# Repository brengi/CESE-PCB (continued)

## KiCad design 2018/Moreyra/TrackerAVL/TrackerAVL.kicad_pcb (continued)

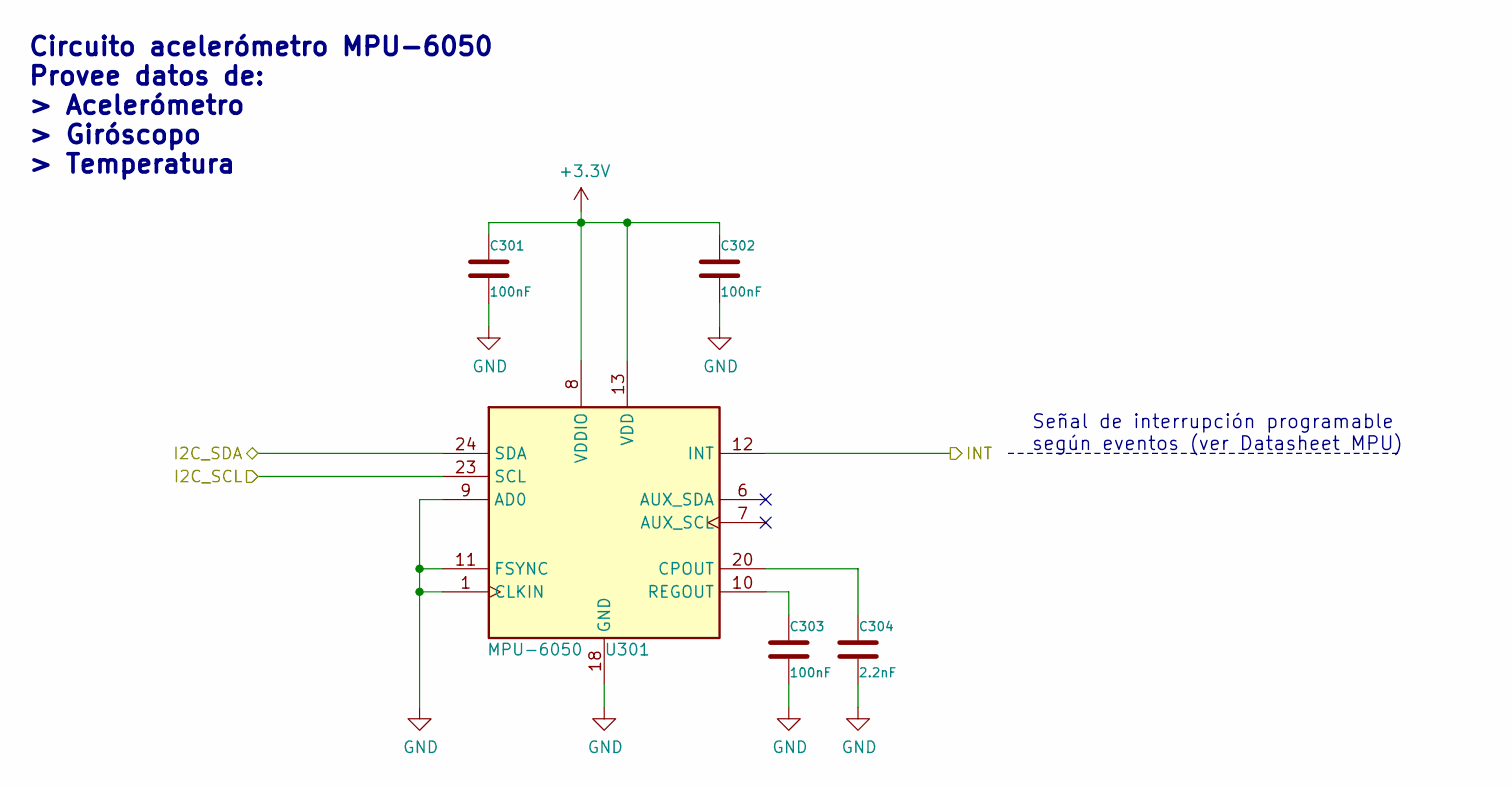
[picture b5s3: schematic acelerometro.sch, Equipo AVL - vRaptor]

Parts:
C301, C302, C303: 100nF; C_0805_2012Metric_Pad1.15x1.40mm_HandSolder
C304: 2.2nF; C_0805_2012Metric_Pad1.15x1.40mm_HandSolder
U301: MPU-6050; InvenSense_QFN-24_4x4mm_P0.5mm

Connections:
+3V3: C301.1, C302.1, U301.8 (VDDIO), U301.13 (VDD); also elsewhere on the board
/Acelerómetro/INT: U301.12 (INT); also elsewhere on the board
/I2C_SCL: U301.23 (SCL); also elsewhere on the board
/I2C_SDA: U301.24 (SDA); also elsewhere on the board
GND: C301.2, C302.2, C303.2, C304.2, U301.1 (CLKIN), U301.9 (AD0), U301.11 (FSYNC), U301.18 (GND); also elsewhere on the board
unnamed: C303.1, U301.10 (REGOUT)
unnamed: C304.1, U301.20 (CPOUT)

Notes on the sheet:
Circuito acelerómetro MPU-6050 Provee datos de: > Acelerómetro > Giróscopo > Temperatura
Señal de interrupción programable según eventos (ver Datasheet MPU)

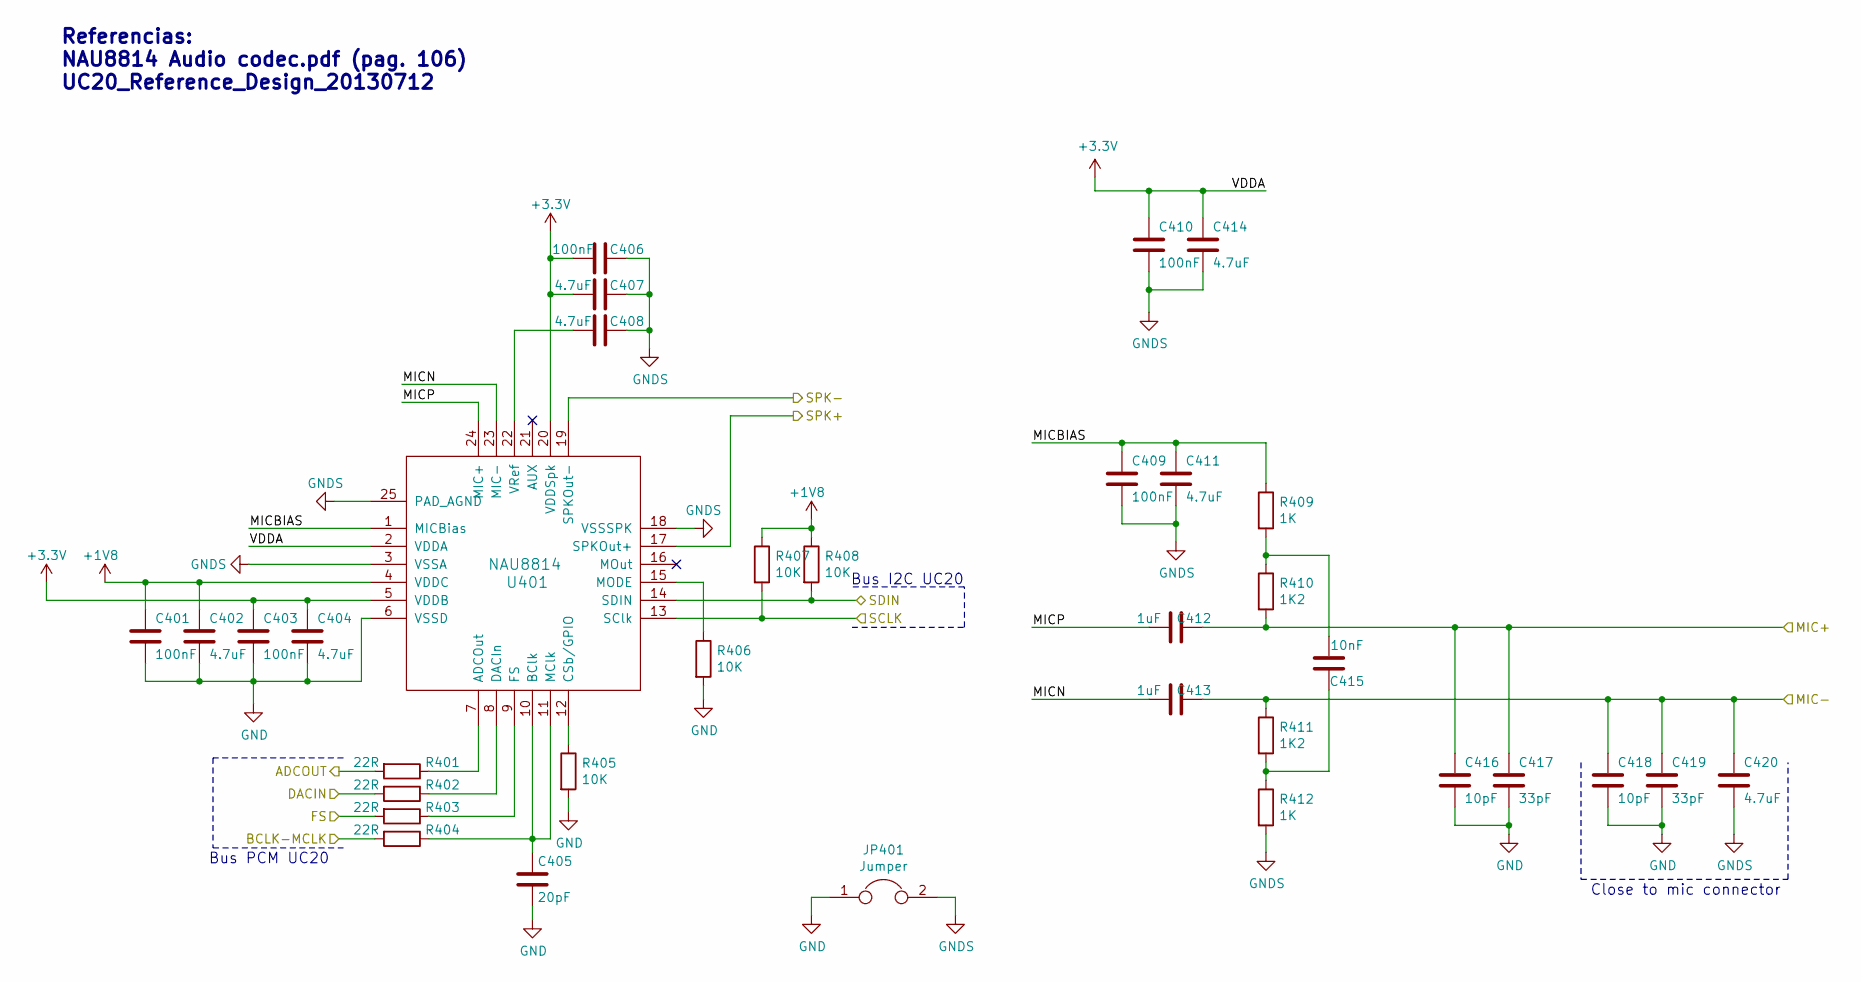
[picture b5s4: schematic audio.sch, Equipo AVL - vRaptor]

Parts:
C401, C403, C406, C409, C410: 100nF; C_0805_2012Metric_Pad1.15x1.40mm_HandSolder
C402, C404, C407, C408, C411, C414, C420: 4.7uF; C_0805_2012Metric_Pad1.15x1.40mm_HandSolder
C405: 20pF; C_0805_2012Metric_Pad1.15x1.40mm_HandSolder
C412, C413: 1uF; C_0805_2012Metric_Pad1.15x1.40mm_HandSolder
C415: 10nF; C_0805_2012Metric_Pad1.15x1.40mm_HandSolder
C416, C418: 10pF; C_0805_2012Metric_Pad1.15x1.40mm_HandSolder
C417, C419: 33pF; C_0805_2012Metric_Pad1.15x1.40mm_HandSolder
JP401: Jumper; SolderJumper-2_P1.3mm_Bridged_Pad1.0x1.5mm
R401, R402, R403, R404: 22R; R_0805_2012Metric_Pad1.15x1.40mm_HandSolder
R405, R406, R407, R408: 10K; R_0805_2012Metric_Pad1.15x1.40mm_HandSolder
R409, R412: 1K; R_0805_2012Metric_Pad1.15x1.40mm_HandSolder
R410, R411: 1K2; R_0805_2012Metric_Pad1.15x1.40mm_HandSolder
U401: NAU8814; NAU8814_QFN-24_4x4mm_Pitch0.5mm_EPAD

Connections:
+1V8: C401.1, C402.1, R407.1, R408.1, U401.4 (VDDC); also elsewhere on the board
+3V3: C403.1, C404.1, C406.1, C407.1, C410.1, C414.1, U401.2 (VDDA), U401.5 (VDDB), U401.20 (VDDSpk); also elsewhere on the board
/Audio/ADCOUT: R401.2; also elsewhere on the board
/Audio/BCLK-MCLK: R404.2; also elsewhere on the board
/Audio/DACIN: R402.2; also elsewhere on the board
/Audio/FS: R403.2; also elsewhere on the board
/Audio/MICBIAS: C409.1, C411.1, R409.1, U401.1 (MICBias)
/Audio/MICN: C413.1, U401.23 (MIC-)
/Audio/MICP: C412.1, U401.24 (MIC+)
/MIC+: C412.2, C416.1, C417.1, R410.2; also elsewhere on the board
/MIC-: C413.2, C418.1, C419.1, C420.1, R411.1; also elsewhere on the board
/SPK+: U401.17 (SPKOut+); also elsewhere on the board
/SPK-: U401.19 (SPKOut-); also elsewhere on the board
/UC20_PCIe/I2C_SCL: R407.2, U401.13 (SClk); also elsewhere on the board
/UC20_PCIe/I2C_SDA: R408.2, U401.14 (SDIN); also elsewhere on the board
GND: C401.2, C402.2, C403.2, C404.2, C405.2, C416.2, C417.2, C418.2, C419.2, JP401.1, R405.2, R406.2, U401.6 (VSSD); also elsewhere on the board
GNDS: C406.2, C407.2, C408.2, C409.2, C410.2, C411.2, C414.2, C420.2, JP401.2, R412.2, U401.3 (VSSA), U401.18 (VSSSPK), U401.25 (PAD_AGND)
unnamed: C405.1, R404.1, U401.10 (BClk), U401.11 (MClk)
unnamed: C408.1, U401.22 (VRef)
unnamed: C415.1, R409.2, R410.1
unnamed: C415.2, R411.2, R412.1
unnamed: R401.1, U401.7 (ADCOut)
unnamed: R402.1, U401.8 (DACIn)
unnamed: R403.1, U401.9 (FS)
unnamed: R405.1, U401.12 (CSb/GPIO)
unnamed: R406.1, U401.15 (MODE)

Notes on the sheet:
Referencias: NAU8814 Audio codec.pdf (pag. 106) UC20_Reference_Design_20130712
Close to mic connector
Bus I2C UC20
Bus PCM UC20

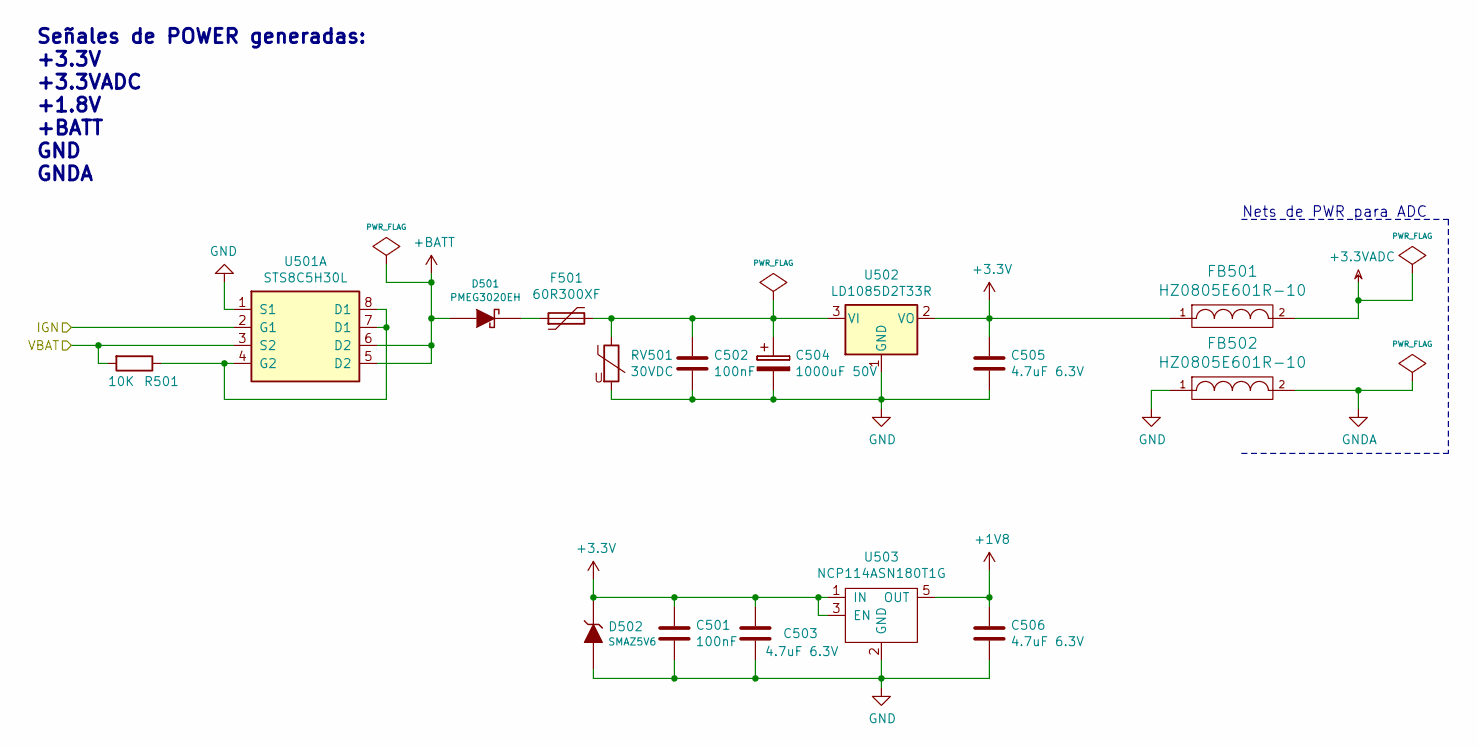
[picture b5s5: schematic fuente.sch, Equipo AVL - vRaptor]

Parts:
C501, C502: 100nF; C_0805_2012Metric_Pad1.15x1.40mm_HandSolder
C503, C505, C506: 4.7uF 6.3V; C_0805_2012Metric_Pad1.15x1.40mm_HandSolder
C504: 1000uF 50V; CP_Radial_D12.5mm_P5.00mm
D501: PMEG3020EH; D_SOD-123F
D502: SMAZ5V6; DO-214AC (SMA)
F501: 60R300XF
FB501, FB502: HZ0805E601R-10; L_0805_2012Metric_Pad1.15x1.40mm_HandSolder
R501: 10K; R_0805_2012Metric_Pad1.15x1.40mm_HandSolder
RV501: 30VDC; D_1206_3216Metric_Pad1.42x1.75mm_HandSolder
U501: STS8C5H30L; SOIC-8_3.9x4.9mm_P1.27mm
U502: LD1085D2T33R; TO-263-3_TabPin2
U503: NCP114ASN180T1G; TSOP-5_NCP114

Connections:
+1V8: C506.1, U503.5 (OUT); also elsewhere on the board
+3.3VADC: FB501.2; also elsewhere on the board
+3V3: C501.1, C503.1, C505.1, D502.2 (K), FB501.1, U502.2 (VO), U503.1 (IN), U503.3 (EN); also elsewhere on the board
+BATT: D501.1 (A), U501.5 (D2), U501.6 (D2)
/IGN: U501.2 (G1); also elsewhere on the board
/VBAT: R501.2, U501.3 (S2); also elsewhere on the board
GND: C501.2, C502.2, C503.2, C504.2, C505.2, C506.2, D502.1 (A), FB502.1, RV501.2, U501.1 (S1), U502.1 (GND), U503.2 (GND); also elsewhere on the board
GNDA: FB502.2; also elsewhere on the board
unnamed: C502.1, C504.1, F501.2, RV501.1, U502.3 (VI)
unnamed: D501.2 (K), F501.1
unnamed: R501.1, U501.4 (G2), U501.7 (D1), U501.8 (VSS)

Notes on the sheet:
Nets de PWR para ADC
Señales de POWER generadas: +3.3V +3.3VADC +1.8V +BATT GND GNDA

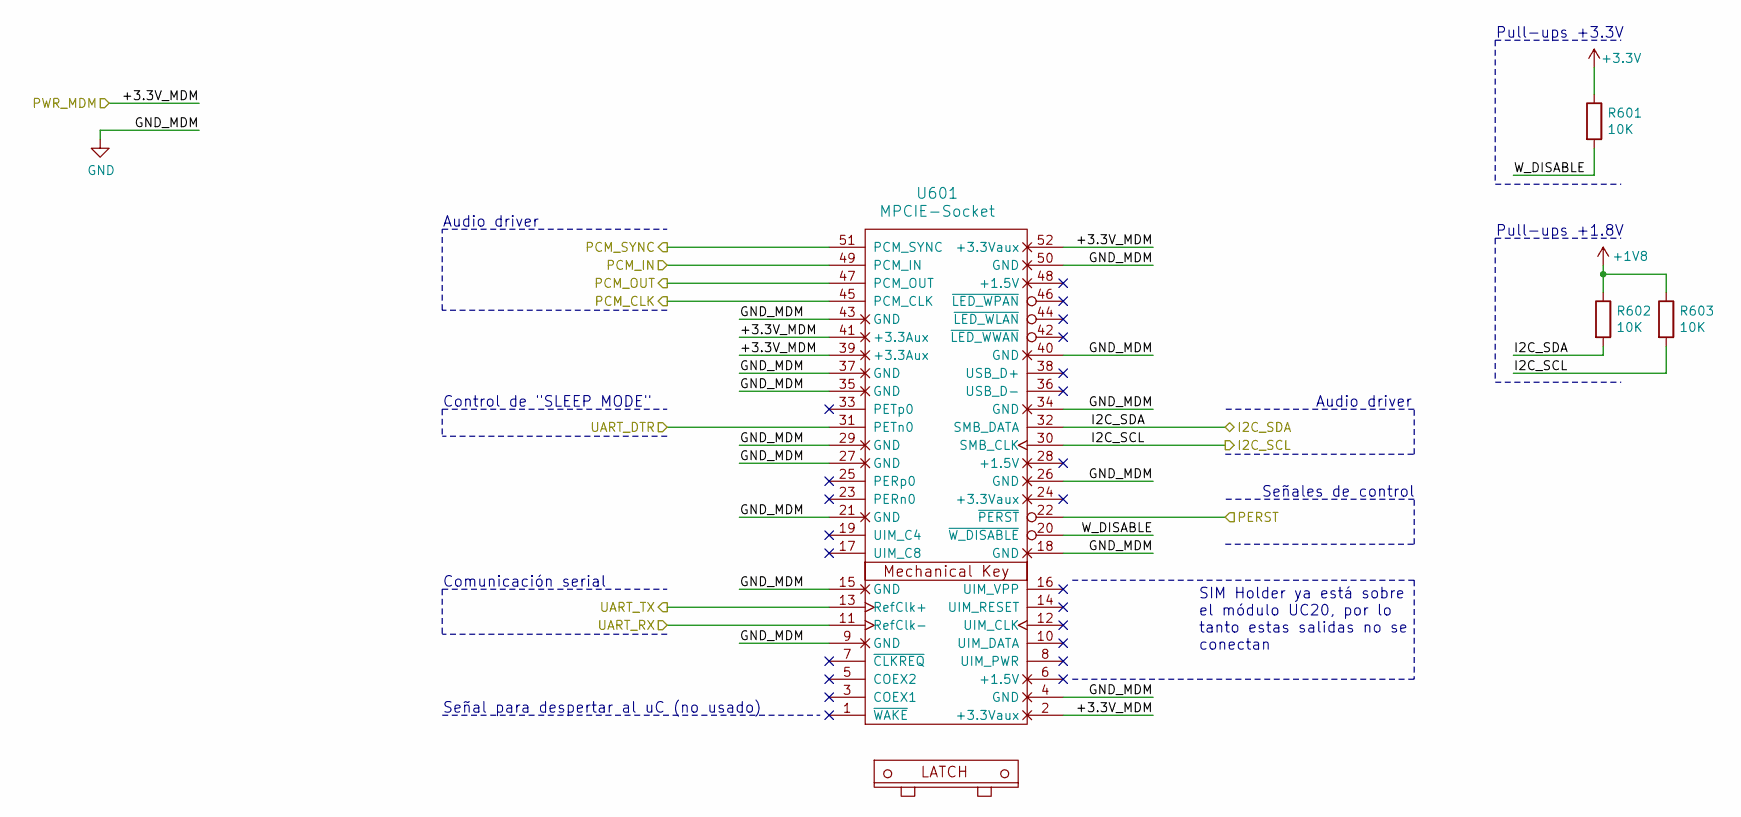
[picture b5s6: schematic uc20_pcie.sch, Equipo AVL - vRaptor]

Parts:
R601, R602, R603: 10K; R_0805_2012Metric_Pad1.15x1.40mm_HandSolder
U601: MPCIE-Socket; mpcie-socket-latch

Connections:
+1V8: R602.1, R603.1; also elsewhere on the board
+3V3: R601.1; also elsewhere on the board
/Audio/ADCOUT: U601.49 (PCM_IN); also elsewhere on the board
/Audio/BCLK-MCLK: U601.45 (PCM_CLK); also elsewhere on the board
/Audio/DACIN: U601.47 (PCM_OUT); also elsewhere on the board
/Audio/FS: U601.51 (PCM_SYNC); also elsewhere on the board
/CPU/PERST: U601.22 (~PERST); also elsewhere on the board
/CPU/PWR_MDM: U601.2 (+3.3Vaux), U601.39 (+3.3Aux), U601.41 (+3.3Aux), U601.52 (+3.3Vaux); also elsewhere on the board
/CPU/SLEEP_MDM: U601.31 (PETn0); also elsewhere on the board
/CPU/U3_RX: U601.13 (RefClk+); also elsewhere on the board
/CPU/U3_TX: U601.11 (RefClk-); also elsewhere on the board
/UC20_PCIe/I2C_SCL: R603.2, U601.30 (SMB_CLK); also elsewhere on the board
/UC20_PCIe/I2C_SDA: R602.2, U601.32 (SMB_DATA); also elsewhere on the board
/UC20_PCIe/W_DISABLE: R601.2, U601.20 (~W_DISABLE)
GND: U601.4 (GND), U601.9 (GND), U601.15 (GND), U601.18 (GND), U601.21 (GND), U601.26 (GND), U601.27 (GND), U601.29 (GND), U601.34 (GND), U601.35 (GND), U601.37 (GND), U601.40 (GND), U601.43 (GND), U601.50 (GND); also elsewhere on the board

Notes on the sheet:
Control de "SLEEP MODE"
Audio driver
Comunicación serial
Pull-ups +3.3V
Pull-ups +1.8V
Señales de control
SIM Holder ya está sobre el módulo UC20, por lo tanto estas salidas no se conectan
Señal para despertar al uC (no usado)

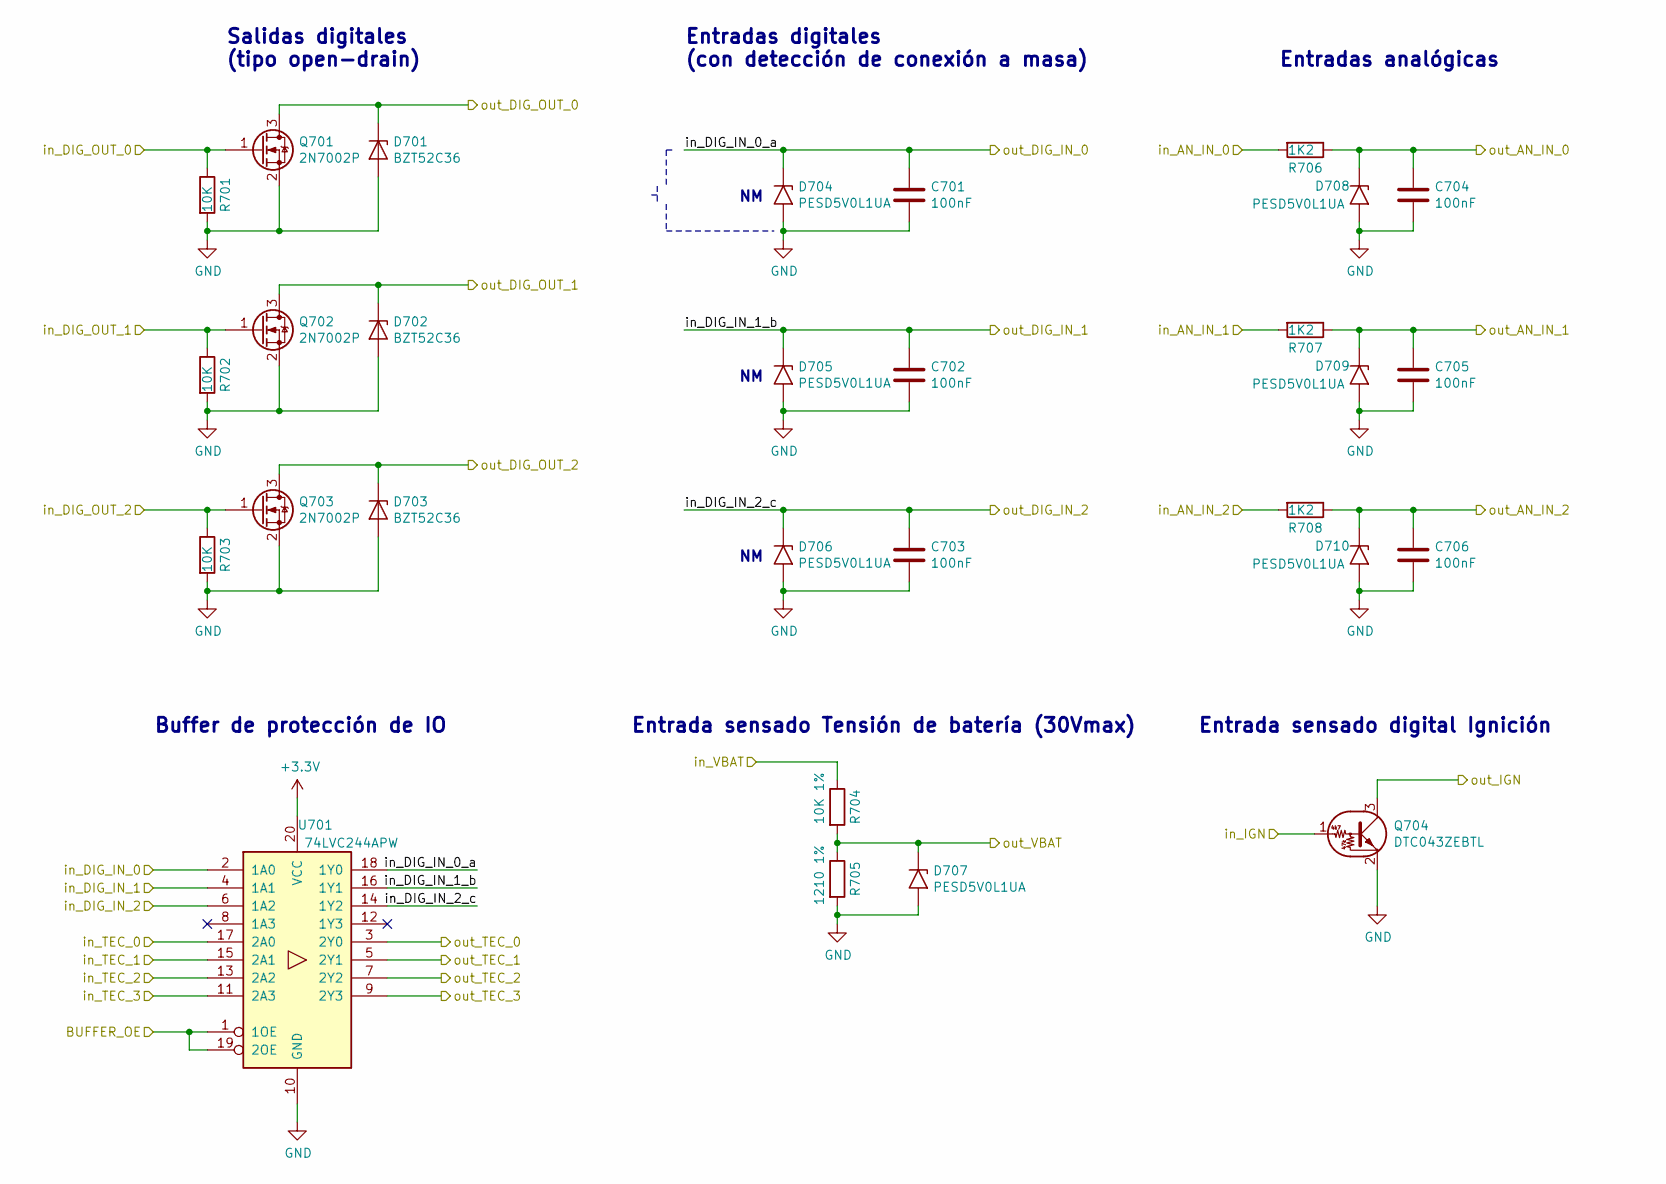
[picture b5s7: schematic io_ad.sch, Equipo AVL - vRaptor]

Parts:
C701, C702, C703, C704, C705, C706: 100nF; C_0805_2012Metric_Pad1.15x1.40mm_HandSolder
D701, D702, D703: BZT52C36; D_SOD-123
D704, D705, D706, D707, D708, D709, D710: PESD5V0L1UA; D_SOD-323_HandSoldering
Q701, Q702, Q703: 2N7002P; SOT-23_Handsoldering
Q704: DTC043ZEBTL; SOT-523_(SOT-416)
R701, R702, R703: 10K; R_0805_2012Metric_Pad1.15x1.40mm_HandSolder
R704: 10K 1%; R_0805_2012Metric_Pad1.15x1.40mm_HandSolder
R705: 1210 1%; R_0805_2012Metric_Pad1.15x1.40mm_HandSolder
R706, R707, R708: 1K2; R_0805_2012Metric_Pad1.15x1.40mm_HandSolder
U701: 74LVC244APW; TSSOP-20_4.4x6.5mm_P0.65mm

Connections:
+3V3: U701.20 (VCC); also elsewhere on the board
/AN_IN_0: R706.2; also elsewhere on the board
/AN_IN_1: R707.2; also elsewhere on the board
/AN_IN_2: R708.2; also elsewhere on the board
/CPU/AN_IN_0: C704.1, D708.1 (A1), R706.1; also elsewhere on the board
/CPU/AN_IN_1: C705.1, D709.1 (A1), R707.1; also elsewhere on the board
/CPU/AN_IN_2: C706.1, D710.1 (A1), R708.1; also elsewhere on the board
/CPU/BUFFER_OE: U701.1 (1OE), U701.19 (2OE); also elsewhere on the board
/CPU/DIG_IN_0: C701.1, D704.1 (A1), U701.18 (1Y0); also elsewhere on the board
/CPU/DIG_IN_1: C702.1, D705.1 (A1), U701.16 (1Y1); also elsewhere on the board
/CPU/DIG_IN_2: C703.1, D706.1 (A1), U701.14 (1Y2); also elsewhere on the board
/CPU/DIG_OUT_0: Q701.1 (G), R701.1; also elsewhere on the board
/CPU/DIG_OUT_1: Q702.1 (G), R702.1; also elsewhere on the board
/CPU/DIG_OUT_2: Q703.1 (G), R703.1; also elsewhere on the board
/CPU/IGN: Q704.3 (C); also elsewhere on the board
/CPU/TEC_0: U701.3 (2Y0); also elsewhere on the board
/CPU/TEC_1: U701.5 (2Y1); also elsewhere on the board
/CPU/TEC_2: U701.7 (2Y2); also elsewhere on the board
/CPU/TEC_3: U701.9 (2Y3); also elsewhere on the board
/CPU/VBAT: D707.1 (A1), R704.2, R705.1; also elsewhere on the board
/DIG_IN_0: U701.2 (1A0); also elsewhere on the board
/DIG_IN_1: U701.4 (1A1); also elsewhere on the board
/DIG_IN_2: U701.6 (1A2); also elsewhere on the board
/DIG_OUT_0: D701.1 (K), Q701.3 (D); also elsewhere on the board
/DIG_OUT_1: D702.1 (K), Q702.3 (D); also elsewhere on the board
/DIG_OUT_2: D703.1 (K), Q703.3 (D); also elsewhere on the board
/IGN: Q704.1 (B); also elsewhere on the board
/TEC_0: U701.17 (2A0); also elsewhere on the board
/TEC_1: U701.15 (2A1); also elsewhere on the board
/TEC_2: U701.13 (2A2); also elsewhere on the board
/TEC_3: U701.11 (2A3); also elsewhere on the board
/VBAT: R704.1; also elsewhere on the board
GND: C701.2, C702.2, C703.2, C704.2, C705.2, C706.2, D701.2 (A), D702.2 (A), D703.2 (A), D704.2 (A2), D705.2 (A2), D706.2 (A2), D707.2 (A2), D708.2 (A2), D709.2 (A2), D710.2 (A2), Q701.2 (S), Q702.2 (S), Q703.2 (S), Q704.2 (E), R701.2, R702.2, R703.2, R705.2, U701.10 (GND); also elsewhere on the board

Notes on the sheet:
Salidas digitales (tipo open-drain)
Entradas digitales (con detección de conexión a masa)
Entradas analógicas
Entrada sensado Tensión de batería (30Vmax)
Entrada sensado digital Ignición
Buffer de protección de IO

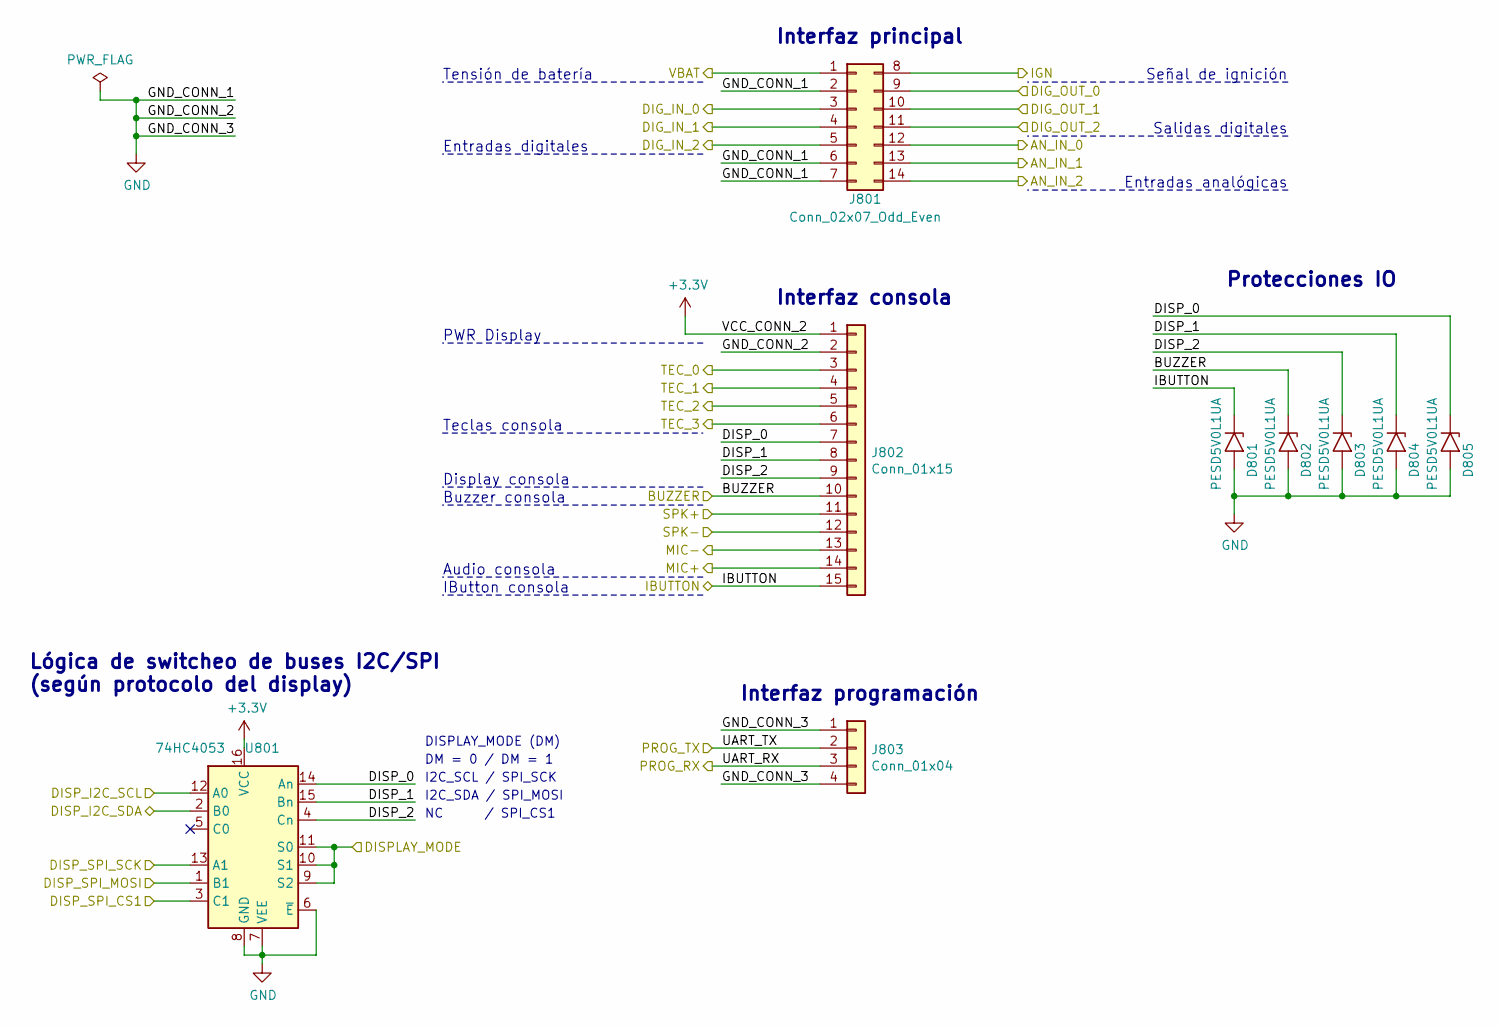
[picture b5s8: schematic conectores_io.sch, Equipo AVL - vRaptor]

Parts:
D801, D802, D803, D804, D805: PESD5V0L1UA; D_SOD-323_HandSoldering
J801: Conn_02x07_Odd_Even; Molex_Micro-Fit_3.0_43045-1406_2x07-1MP_P3.00mm_Horizontal
J802: Conn_01x15; Molex_Pico_SPOX_87438-0443_1x15
J803: Conn_01x04; Molex_Pico_SPOX_87438-0443_1x04
U801: 74HC4053; SOIC-16_3.9x9.9mm_P1.27mm

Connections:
+3V3: J802.1, U801.16 (VCC); also elsewhere on the board
/AN_IN_0: J801.12; also elsewhere on the board
/AN_IN_1: J801.13; also elsewhere on the board
/AN_IN_2: J801.14; also elsewhere on the board
/CPU/BUZZER: D802.1 (A1), J802.10; also elsewhere on the board
/CPU/DISPLAY_MODE: U801.9 (S2), U801.10 (S1), U801.11 (S0); also elsewhere on the board
/CPU/IBUTTON: D801.1 (A1), J802.15; also elsewhere on the board
/Conectores_IO/DISP_0: D805.1 (A1), J802.7, U801.14 (An)
/Conectores_IO/DISP_1: D804.1 (A1), J802.8, U801.15 (Bn)
/Conectores_IO/DISP_2: D803.1 (A1), J802.9, U801.4 (Cn)
/Conectores_IO/DISP_SPI_CS1: U801.3 (C1); also elsewhere on the board
/Conectores_IO/PROG_RX: J803.3; also elsewhere on the board
/Conectores_IO/PROG_TX: J803.2; also elsewhere on the board
/DIG_IN_0: J801.3; also elsewhere on the board
/DIG_IN_1: J801.4; also elsewhere on the board
/DIG_IN_2: J801.5; also elsewhere on the board
/DIG_OUT_0: J801.9; also elsewhere on the board
/DIG_OUT_1: J801.10; also elsewhere on the board
/DIG_OUT_2: J801.11; also elsewhere on the board
/I2C_SCL: U801.12 (A0); also elsewhere on the board
/I2C_SDA: U801.2 (B0); also elsewhere on the board
/IGN: J801.8; also elsewhere on the board
/MIC+: J802.14; also elsewhere on the board
/MIC-: J802.13; also elsewhere on the board
/SPI_MOSI: U801.1 (B1); also elsewhere on the board
/SPI_SCK: U801.13 (A1); also elsewhere on the board
/SPK+: J802.11; also elsewhere on the board
/SPK-: J802.12; also elsewhere on the board
/TEC_0: J802.3; also elsewhere on the board
/TEC_1: J802.4; also elsewhere on the board
/TEC_2: J802.5; also elsewhere on the board
/TEC_3: J802.6; also elsewhere on the board
/VBAT: J801.1; also elsewhere on the board
GND: D801.2 (A2), D802.2 (A2), D803.2 (A2), D804.2 (A2), D805.2 (A2), J801.2, J801.6, J801.7, J802.2, J803.1, J803.4, U801.6 (~E), U801.7 (VEE), U801.8 (GND); also elsewhere on the board

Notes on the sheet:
PWR Display
Teclas consola
Display consola
Audio consola
IButton consola
Entradas digitales
Tensión de batería
Señal de ignición
Salidas digitales
Entradas analógicas
Interfaz principal
Interfaz consola
Interfaz programación
Protecciones IO
Buzzer consola
Lógica de switcheo de buses I2C/SPI (según protocolo del display)
I2C_SCL / SPI_SCK
I2C_SDA / SPI_MOSI
NC / SPI_CS1
DM = 0 / DM = 1
DISPLAY_MODE (DM)

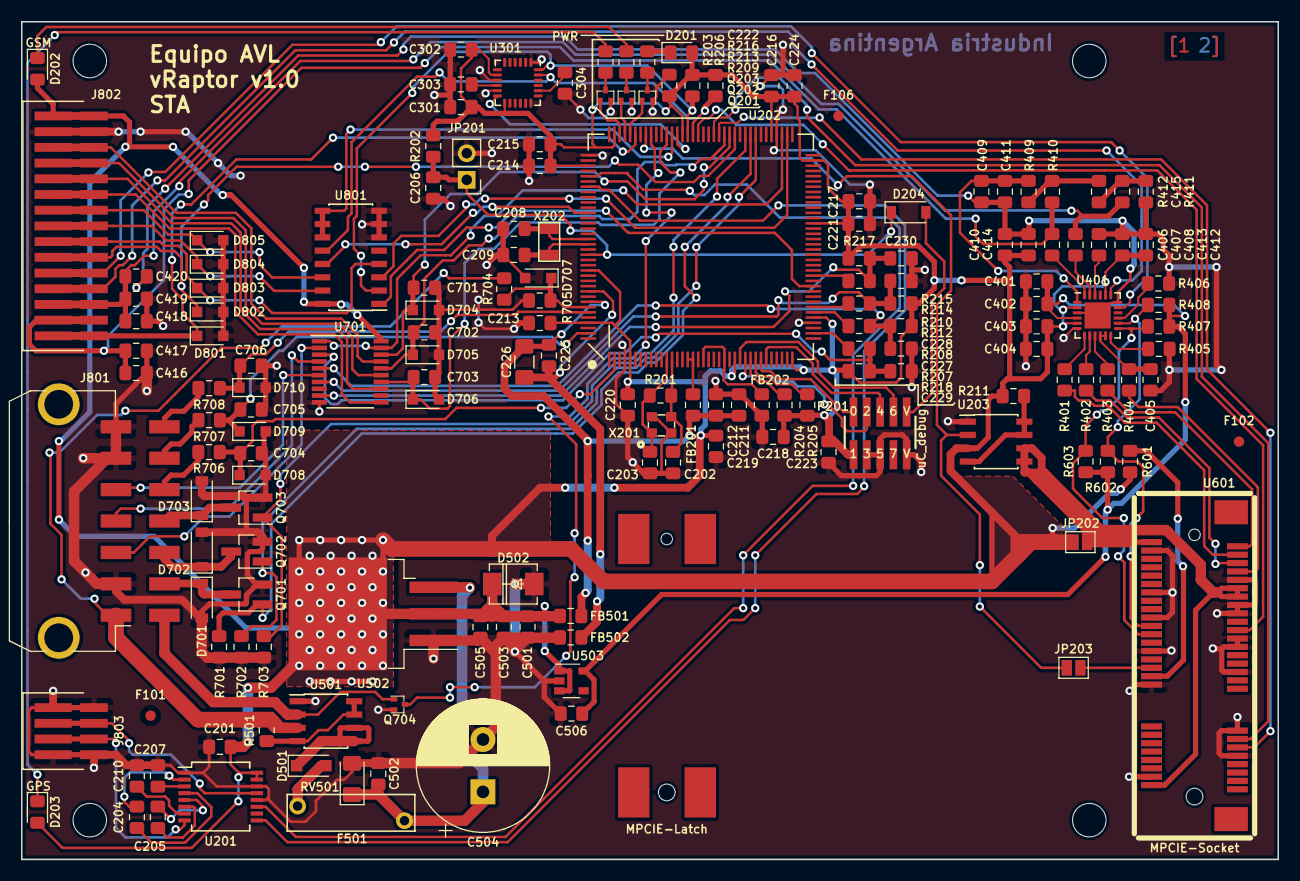
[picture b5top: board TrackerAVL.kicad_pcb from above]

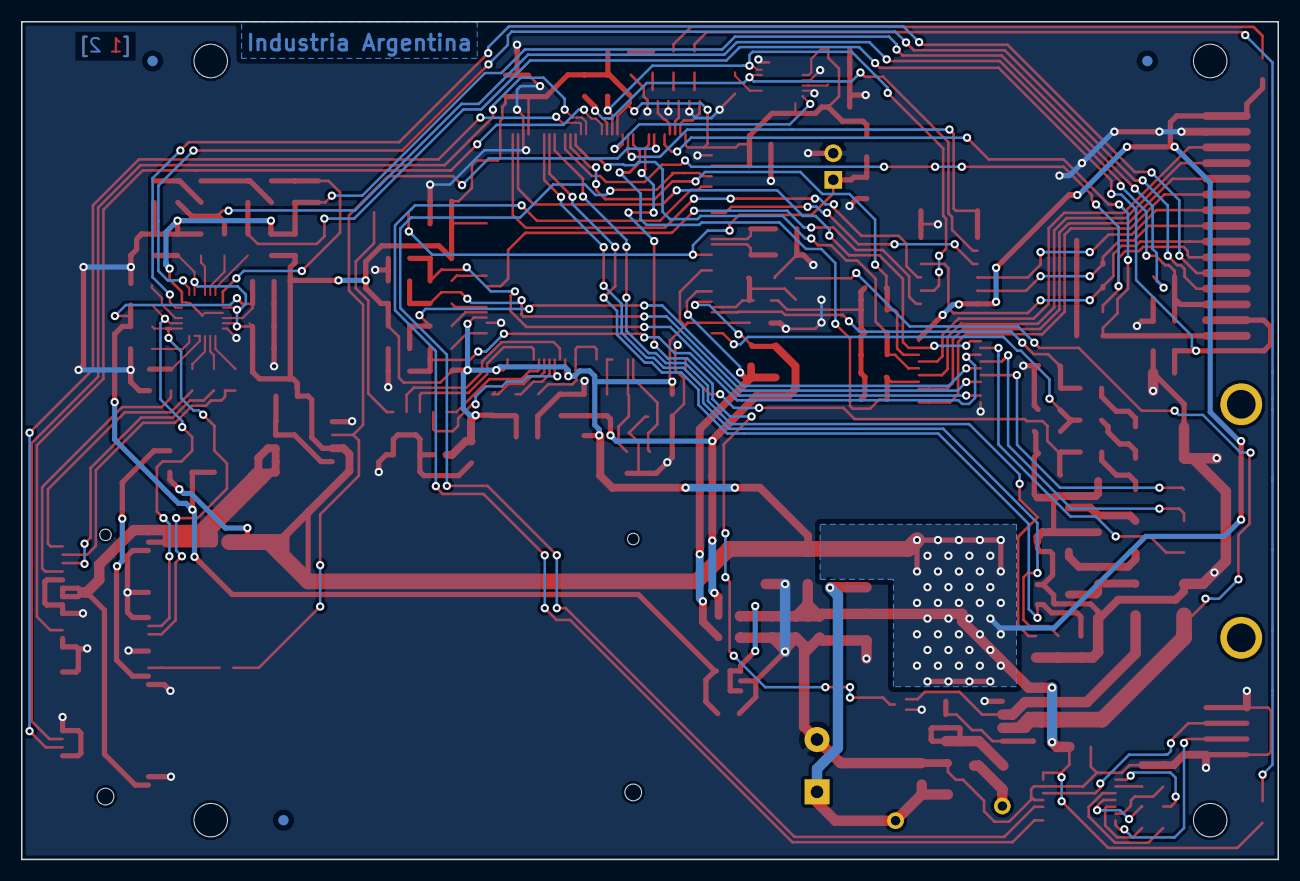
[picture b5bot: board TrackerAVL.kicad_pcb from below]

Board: 2 copper layers, 120.0 x 80.0 mm, 173 parts (3 on the bottom side), 122 nets.

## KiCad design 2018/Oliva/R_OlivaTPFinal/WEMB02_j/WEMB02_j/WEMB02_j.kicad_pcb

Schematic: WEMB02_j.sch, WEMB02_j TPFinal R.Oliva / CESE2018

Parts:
F101, F102, F103: Fiducial; Fiducial_1mm_Dia_2mm_Outer
MH101, MH102, MH103, MH104: MH4mm; MountingHole_4mm

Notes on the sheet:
PLACA MADRE - WIND EMPOWERMENT WEMB02 CONTROL Y ALIMENTACION MÓDULOS DE POTENCIA PARA SOLAR / EOLICA REV. WEMB02J - R.OLIVA 8.12.2018

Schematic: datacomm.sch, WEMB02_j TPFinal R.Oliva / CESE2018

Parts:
C201, C203: 0.1uF 50V; C_0805_2012Metric_Pad1.15x1.40mm_HandSolder
C202: 4.7uF 50V MLCC; C_1210_3225Metric_Pad1.42x2.65mm_HandSolder
D201: CDSOT23-SM712; SOT-323_SC-70_Handsoldering
FR201: 1.5A; C_Disc_D4.3mm_W1.9mm_P5.00mm
J201: Conn_01x05; Molex_KK-254_AE-6410-05A_1x05_P2.54mm_Vertical
J202: RasPI_IO_Header; PinHeader_2x13_P2.54mm_Vertical
J203: RS485; TerminalBlock_bornier-3_P5.08mm
JP201: RX TO RBPI/ARD; PinHeader_1x03_P2.54mm_Vertical
JP202: TX_FROM RBPI/ARD; PinHeader_1x03_P2.54mm_Vertical
JP203: DIR_485 FROM RBPI/ARD; PinHeader_1x03_P2.54mm_Vertical
JP204: +3V3RBPI/+5VARD; PinHeader_1x03_P2.54mm_Vertical
JP205: TER; PinHeader_1x02_P2.54mm_Vertical
Q201: IRFR9024; TO-252-3_TabPin4
R201: 100K; R_0805_2012Metric_Pad1.15x1.40mm_HandSolder
R202: 1K; R_0805_2012Metric_Pad1.15x1.40mm_HandSolder
R203, R204, R205: 10K; R_0805_2012Metric_Pad1.15x1.40mm_HandSolder
R206, R207: 47R; R_0805_2012Metric_Pad1.15x1.40mm_HandSolder
R208: 120R; R_0805_2012Metric_Pad1.15x1.40mm_HandSolder
TP201: +5VLtp; TestPoint_THTPad_D2.0mm_Drill1.0mm
TP202: GNDS; TestPoint_THTPad_D2.0mm_Drill1.0mm
U201: SN75HVD08; SOIC-8_3.9x4.9mm_P1.27mm
XA201: Arduino_Mega2560_Shield; arduino_mega_header

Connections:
+3V3: JP204.3; also elsewhere on the board
+5VL: C201.1, C202.1, J201.5, J202.2, J202.4, Q201.3, TP201.1, XA201.5, XA201.42, XA201.60
+5VP: FR201.1, JP204.1; also elsewhere on the board
/DataComm/B_OUT: D201.2, J203.2, R206.1, R208.2
/DataComm/D485_RBPI: J202.22, JP203.3
/DataComm/DIR_485_ARD: JP203.1, XA201.73
/DataComm/RESET_4D: J201.2, R202.1
/DataComm/RX1_DISP: J201.4, XA201.63
/DataComm/RX2_ARD: JP201.1, XA201.65
/DataComm/RX_TO_RBPI: J202.10, JP201.3
/DataComm/TX1_DISP: J201.3, XA201.64
/DataComm/TX2_ARD: JP202.1, XA201.66
/DataComm/TX_FROM_RBPI(TX0_14): J202.8, JP202.3
GNDS: C201.2, C202.2, C203.2, D201.3, J201.1, J202.9, J202.14, J202.20, J202.25, J203.3, R201.2, R203.2, R205.2, TP202.1, U201.5 (GND), XA201.6, XA201.7, XA201.25, XA201.43, XA201.83; also elsewhere on the board
unnamed: C203.1, JP204.2, R204.1, U201.8 (VCC)
unnamed: D201.1, J203.1, JP205.2, R207.1
unnamed: FR201.2, Q201.2
unnamed: JP201.2, R204.2, U201.1 (RO)
unnamed: JP202.2, R205.1, U201.4 (DI)
unnamed: JP203.2, R203.1, U201.2 (~RE), U201.3 (DE)
unnamed: JP205.1, R208.1
unnamed: Q201.1, R201.1
unnamed: R202.2, XA201.74
unnamed: R206.2, U201.7 (B)
unnamed: R207.2, U201.6 (A)

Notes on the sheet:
REVERSE POL & BACK-SUPP PROT.
TVS DUAL CDSOT23-SM712
GND B A
4D DISPLAY CONNECTOR TX1/RX1/RESET
ARD/RBPI RS485 SELECTORS JP301-303 1:2 ARDUINO 2:3 RBPI
RBPI STD CONN POWER +5V ISO & COMM PORT, DIR 3V3 TTL LEVEL (RBPI UNDER WEMB02)
TI SN75HVD08 RS485 5V/3.3V CONVERTER W/OUTPUT PROT. STD A,B,GND CONN
TERMINATION 120R RESISTOR - JP305 =ON
RS485 SUPPLY JP304 5V (1-2 JUMPER) FOR ARD 3V3 (2-3 JUMPER) FOR RBPI
ARDUINO MEGA2560 MONTAJE DEBAJO DE PLACA WEMB02
+5VL es +5VP luego de Q301, Reverse-Protection
MODULO CONTROL ARDUINO-MEGA
MODULO RS485
CONECTOR A RASPBERRY-PI

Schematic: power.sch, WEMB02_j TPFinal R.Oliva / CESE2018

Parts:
BAT(+)301: SCREW_TERM8191; Banana_Jack_1Pin
BAT(-)301: SCREW_TERM8191; Banana_Jack_1Pin
C301, C305: 0.1uF 50V MLCC; C_0805_2012Metric_Pad1.15x1.40mm_HandSolder
C302: 0.1uF 50V; C_0805_2012Metric_Pad1.15x1.40mm_HandSolder
C303, C306: 10uF 50V MLCC; C_1210_3225Metric_Pad1.42x2.65mm_HandSolder
C304: 10uF 50V; C_1210_3225Metric_Pad1.42x2.65mm_HandSolder
CR301: SMAJ70A
CR302: SMAJ15A; SMAJ70A
CR303: SMAJ05A; SMAJ70A
D301, D302, D303: +5V_F ON; LED_0805_2012Metric_Pad1.15x1.40mm_HandSolder
FR301: 2.7 A; C_Disc_D16.0mm_W5.0mm_P10.00mm
FR302: 1.5A; C_Disc_D4.3mm_W1.9mm_P5.00mm
J301: EXP_PWR; TerminalBlock_RND_205-00232_1x02_P5.08mm_Horizontal
JF301, JF302: Screw_Terminal_01x06; TerminalBlock_bornier-6_P5.08mm
JP301, JP304, JP305: Jumper_2_Open; PinHeader_1x02_P2.54mm_Vertical
JP302, JP303: MAN/-AUTO; PinHeader_1x03_P2.54mm_Vertical
Q301, Q302: BC817-40_215; BC817-40; MPN BC817-40,215; Digi-Key_PN 1727-2919-1-ND
R301, R305, R306: 10K; R_0805_2012Metric_Pad1.15x1.40mm_HandSolder
R302, R303: 5K; R_0805_2012Metric_Pad1.15x1.40mm_HandSolder
R304, R307: 100K; R_0805_2012Metric_Pad1.15x1.40mm_HandSolder
RV301: 10 K MT; PV36W103C01B00
TP_GND301: TP2; TestPoint_THTPad_D2.0mm_Drill1.0mm
U301: SDM30-125S; POWER_SDM1b
U302: FEEDER_BRD; Global_feeder
U303: R-78E3.3-0.5; Converter_DCDC_RECOM_R-78E-0.5_THT
U304: R-78E5.0-1.0; Converter_DCDC_RECOM_R-78E-0.5_THT

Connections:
+3V3: C303.1, U303.3 (OUT); also elsewhere on the board
+5F: C306.1, CR303.1, JF301.2, JF301.5, JF302.2, JF302.5, JP304.1, U304.3 (OUT)
+5VP: C301.1, C302.2, FR302.2, JP305.1, U301.6, U303.1 (IN); also elsewhere on the board
+15V: C304.1, C305.1, CR302.1, JF301.1, JF301.4, JF302.1, JF302.4, JP301.1, R307.2, U301.1, U302.4, U304.1 (IN)
+BATT: BAT(+)301.1, FR301.2; also elsewhere on the board
/LowV_Detect/-FEED_SHDN: R305.1; also elsewhere on the board
/Power/+B_FEED: CR301.1, FR301.1, R304.2, U302.1
/Power/-FSHDN: JP302.2, R304.1, U302.3
/Power/SDM1: R306.1; also elsewhere on the board
/Power/SDM_ON: JP303.2, R307.1, U301.4
Earth: BAT(-)301.1, C304.2, C305.2, C306.2, CR301.2, CR302.2, CR303.2, D301.1, D302.1, JF301.3, JF301.6, JF302.3, JF302.6, JP302.3, JP303.3, Q301.2, Q302.2, TP_GND301.1, U301.2, U302.2, U302.5, U304.2 (GND); also elsewhere on the board
GNDS: C301.2, C302.1, C303.2, D303.1, J301.2, RV301.1, U301.7, U303.2 (GND); also elsewhere on the board
unnamed: D301.2, R301.2
unnamed: D302.2, R302.2
unnamed: D303.2, R303.2
unnamed: FR302.1, J301.1
unnamed: JP301.2, R301.1
unnamed: JP302.1, Q301.3
unnamed: JP303.1, Q302.3
unnamed: JP304.2, R302.1
unnamed: JP305.2, R303.1
unnamed: Q301.1, R305.2
unnamed: Q302.1, R306.2
unnamed: RV301.2, RV301.3, U301.8

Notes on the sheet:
INPUTS FROM BATTERY
-SHDN de LM5576 SI OPEN: PULL UP INTERNO A ON LOW: SHUTDOWN MODE
SDM30-12S5 ISOLATED DC/DC CONV +5V OUT 5A MAX 2"X2" PCB PACKAGE (BOTTOM SIDE)
FEEDER BOARD J.ALINEI 2016
TO POWER MODULES
UP-TRIM +VOUT
70V TVS
15V TVS
5V TVS
JP FEEDER 1-2 LVD_AUTO 2-3 OFF ALL OPEN: ON
JP +5V ISO 1-2 LVD_AUTO 2-3 OFF ALL OPEN: ON
78E05 RECOM SWITCHING DC/DC CONV +5V OUT 1A MAX PTH
78E03.3 RECOM SWITCHING DC/DC CONV +3V3 OUT 0.5A MAX PTH
(+5V) GNDS
ENTRADA DESDE BATERIAS
MODULO FEEDER PRINCIPAL +15V
SALIDAS FEEDER PRINCIPAL Y EXPANSION
SUB MODULO FEEDER SALIDA +5V
MODULO ISO +5V/5A, +3V3 Y LED
LVD INPUT
FEEDER LEDs
